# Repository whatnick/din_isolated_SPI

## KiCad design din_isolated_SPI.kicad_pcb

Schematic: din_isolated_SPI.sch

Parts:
C1, C2: 100nF; C_0603
G1: LOGO; Whatnick_logo
J1: CONN_01X10; Molex_MicroLatch-53253-1070_10x2.00mm_Straight
LOGO1: Logo_Open_Hardware_Small; OSHW-Symbol_6.7x6mm_SilkScreen
R1, R2, R3, R4, R5, R6, R7, R8, R9, R10, R11, R12: 50R; R_0603
U1: SI8661AB-B-IS1; SOIC-16_3.9x9.9mm_Pitch1.27mm
U4: WeMos_mini; D1_mini_board

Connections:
3V3_C: C2.1, J1.1, U1.1, U4.16
3V3_I: C1.1, J1.10, U1.16
CLK_E: J1.5, R7.1
CLK_W: R1.2, U4.12
CS0_E: J1.4, R9.1
CS0_W: R3.2, U4.15
CS1_E: J1.8, R10.1
CS1_W: R4.2, U4.4
CS2_E: J1.3, R11.1
CS2_W: R5.2, U4.3
GND_C: C2.2, J1.2, U1.8, U4.2
GND_I: C1.2, J1.9, U1.9
MISO_E: J1.6, R12.1
MISO_W: R6.2, U4.13
MOSI_E: J1.7, R8.1
MOSI_W: R2.2, U4.14
unnamed: R1.1, U1.2
unnamed: R2.1, U1.3
unnamed: R3.1, U1.4
unnamed: R4.1, U1.5
unnamed: R5.1, U1.6
unnamed: R6.1, U1.7
unnamed: R7.2, U1.15
unnamed: R8.2, U1.14
unnamed: R9.2, U1.13
unnamed: R10.2, U1.12
unnamed: R11.2, U1.11
unnamed: R12.2, U1.10

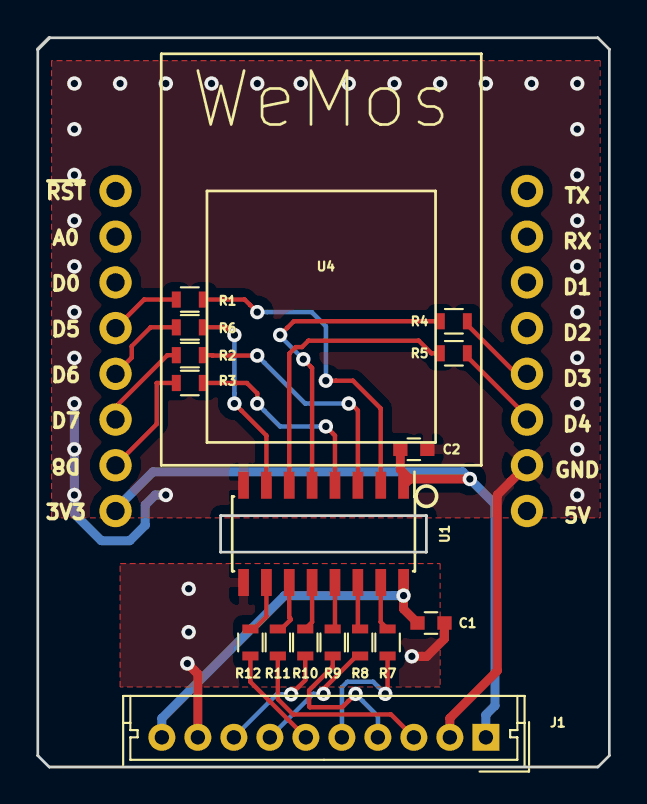
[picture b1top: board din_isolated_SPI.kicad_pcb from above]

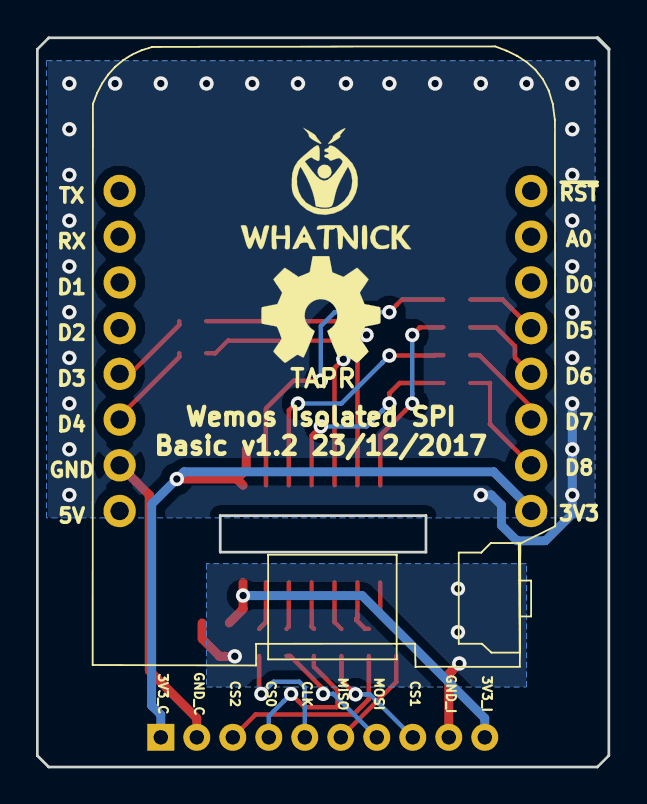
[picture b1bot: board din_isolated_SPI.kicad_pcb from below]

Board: 2 copper layers, 31.8 x 40.5 mm, 19 parts (3 on the bottom side), 28 nets.

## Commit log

2017-10-28 initial
2017-10-28 Added datasheets
2017-10-29 Autorouted basic isolated SPI
2017-10-29 Added logos
2017-10-29 Added stitching vias and silk screen detail
2017-10-30 Finalize silk screen and gerbers
2017-10-30 Update component map
2017-11-22 small silk screen change
2017-12-23 Change to 0603 and reroute
2017-12-23 New gerbers
2017-12-23 Fix silk screens
2018-09-10 Port to new kicad
2018-09-10 Create new BOM
2019-04-19 Change referenced to model
2019-06-05 New 3dmodels
